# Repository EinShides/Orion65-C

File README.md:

A 65% keyboard PCB that supports standard and arrow key blocker layouts (such as the kbd67) and stepped caps lock. The PCB also features a flex cut for a softer typing experience. Uses USB type C and has a ESD protection diode. PCB is tested and working. A matching case model can be found here via the fusion 360 link: https://a360.co/2X7CGb7 (Though there is a name engraving for myself in the top right that needs to be changed if you don't want it).

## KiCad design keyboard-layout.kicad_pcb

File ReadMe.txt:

The Orion65 pcb is a minimalistic 65% keybaord that is based off and inspired by the voyager60 PCB made by ai03. This PCB uses the same mounting holes as the tada68.

IMPORTANT: Make sure to check and meet the design rules of the chosen pcb manufacturer before ordering or else errors may occur.
		e.g. OSH Park recommends a Pad Mask Clearance of 0.0508mm

This CAD file was created in Kicad version (5.1.5)-3, release build.

Application: KiCad
Version: (5.1.5)-3, release build
Libraries:
    wxWidgets 3.0.4
    libcurl/7.66.0 OpenSSL/1.1.1d (Schannel) zlib/1.2.11 brotli/1.0.7 libidn2/2.2.0 libpsl/0.21.0 (+libidn2/2.1.1) nghttp2/1.39.2
Platform: Windows 8 (build 9200), 64-bit edition, 64 bit, Little endian, wxMSW
Build Info:
    wxWidgets: 3.0.4 (wchar_t,wx containers,compatible with 2.8)
    Boost: 1.71.0
    OpenCASCADE Community Edition: 6.9.1
    Curl: 7.66.0
    Compiler: GCC 9.2.0 with C++ ABI 1013

Build settings:
    USE_WX_GRAPHICS_CONTEXT=OFF
    USE_WX_OVERLAY=OFF
    KICAD_SCRIPTING=ON
    KICAD_SCRIPTING_MODULES=ON
    KICAD_SCRIPTING_PYTHON3=OFF
    KICAD_SCRIPTING_WXPYTHON=ON
    KICAD_SCRIPTING_WXPYTHON_PHOENIX=OFF
    KICAD_SCRIPTING_ACTION_MENU=ON
    BUILD_GITHUB_PLUGIN=ON
    KICAD_USE_OCE=ON
    KICAD_USE_OCC=OFF
    KICAD_SPICE=ON

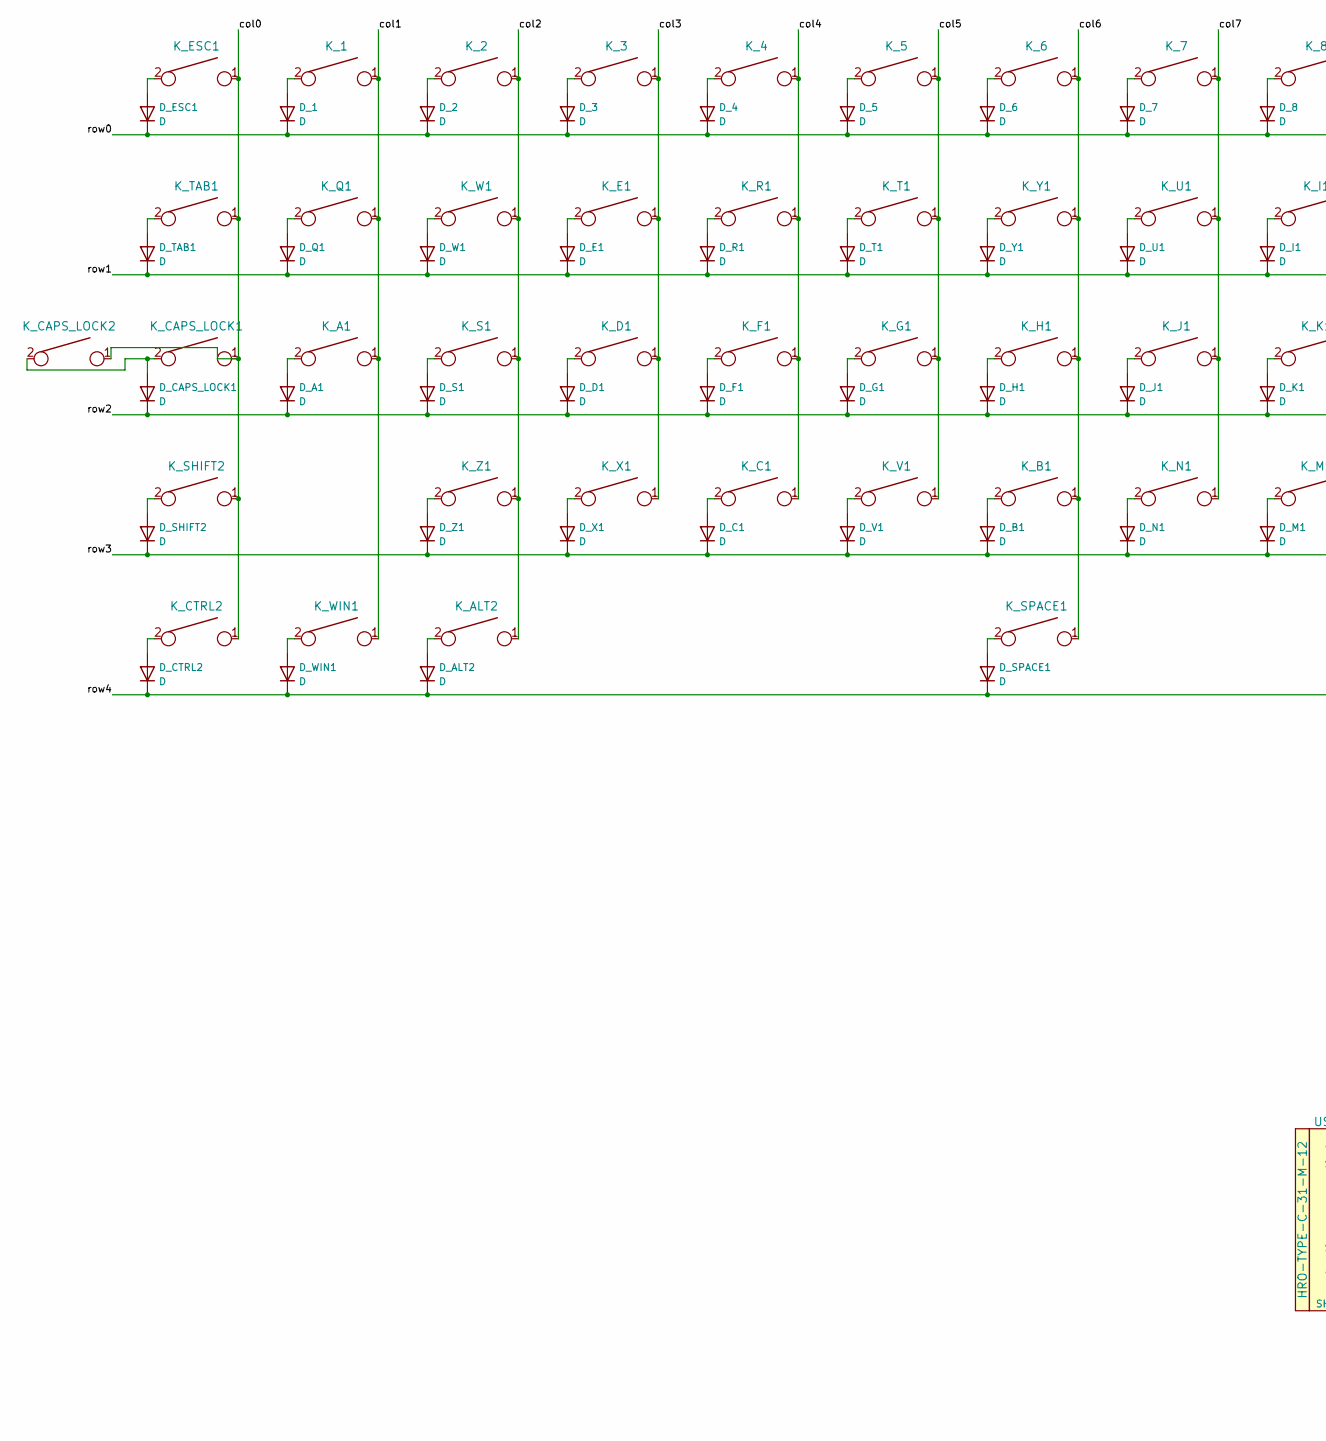
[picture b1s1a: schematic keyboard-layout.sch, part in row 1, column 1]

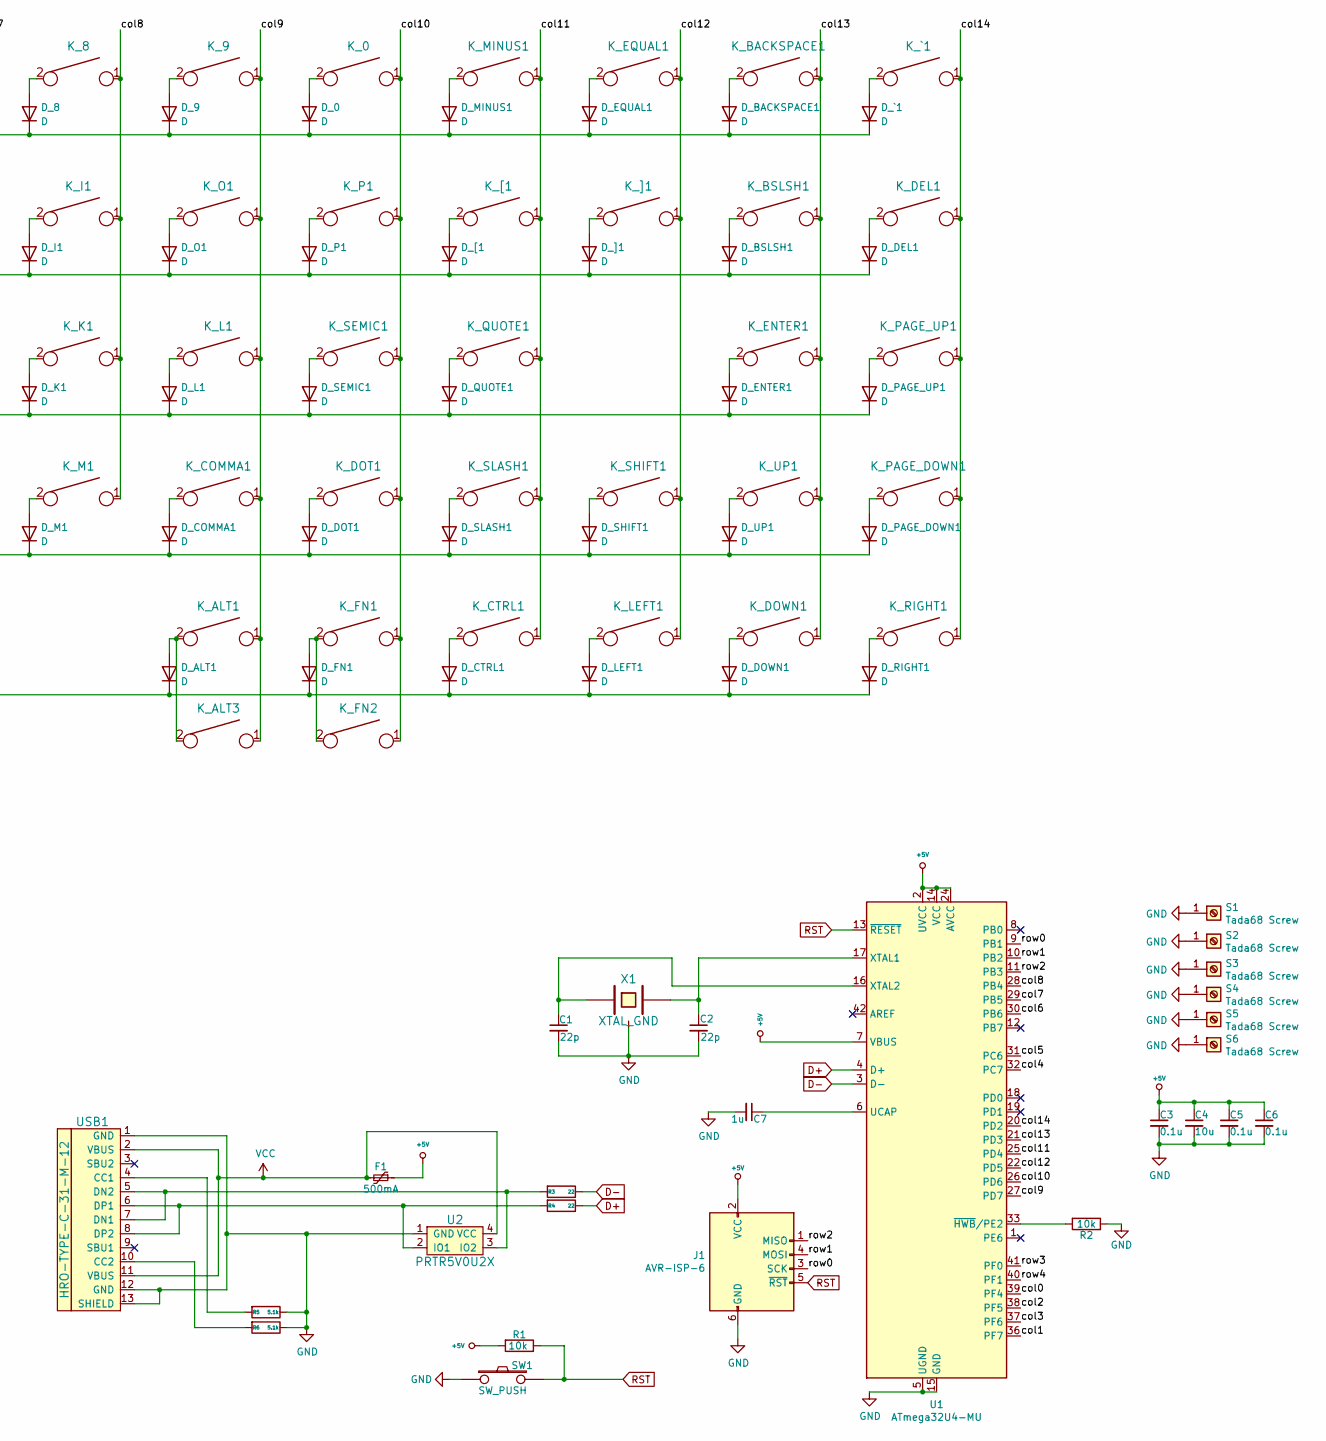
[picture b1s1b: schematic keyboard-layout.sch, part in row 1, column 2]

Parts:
C1, C2: 22p; C_0603_1608Metric_Pad1.05x0.95mm_HandSolder; LCSC C1653
C3, C5, C6: 0.1u; C_0603_1608Metric_Pad1.05x0.95mm_HandSolder; LCSC C24452
C4: 10u; C_0603_1608Metric_Pad1.05x0.95mm_HandSolder; LCSC C96446
C7: 1u; C_0603_1608Metric_Pad1.05x0.95mm_HandSolder; LCSC C15849
D_0, D_1, D_2, D_3, D_4, D_5, D_6, D_7, D_8, D_9: D; D_SOD123_hand; LCSC C64898
D_A1: D; D_SOD123_hand; LCSC C64898
D_ALT1, D_ALT2: D; D_SOD123_hand; LCSC C64898
D_B1: D; D_SOD123_hand; LCSC C64898
D_BACKSPACE1: D; D_SOD123_hand; LCSC C64898
D_BSLSH1: D; D_SOD123_hand; LCSC C64898
D_C1: D; D_SOD123_hand; LCSC C64898
D_CAPS_LOCK1: D; D_SOD123_hand; LCSC C64898
D_COMMA1: D; D_SOD123_hand; LCSC C64898
D_CTRL1, D_CTRL2: D; D_SOD123_hand; LCSC C64898
D_D1: D; D_SOD123_hand; LCSC C64898
D_DEL1: D; D_SOD123_hand; LCSC C64898
D_DOT1: D; D_SOD123_hand; LCSC C64898
D_DOWN1: D; D_SOD123_hand; LCSC C64898
D_E1: D; D_SOD123_hand; LCSC C64898
D_ENTER1: D; D_SOD123_hand; LCSC C64898
D_EQUAL1: D; D_SOD123_hand; LCSC C64898
D_ESC1: D; D_SOD123_hand; LCSC C64898
D_F1: D; D_SOD123_hand; LCSC C64898
D_FN1: D; D_SOD123_hand; LCSC C64898
D_G1: D; D_SOD123_hand; LCSC C64898
D_H1: D; D_SOD123_hand; LCSC C64898
D_I1: D; D_SOD123_hand; LCSC C64898
D_J1: D; D_SOD123_hand; LCSC C64898
D_K1: D; D_SOD123_hand; LCSC C64898
D_L1: D; D_SOD123_hand; LCSC C64898
D_LEFT1: D; D_SOD123_hand; LCSC C64898
D_M1: D; D_SOD123_hand; LCSC C64898
D_MINUS1: D; D_SOD123_hand; LCSC C64898
D_N1: D; D_SOD123_hand; LCSC C64898
D_O1: D; D_SOD123_hand; LCSC C64898
D_P1: D; D_SOD123_hand; LCSC C64898
D_PAGE_DOWN1: D; D_SOD123_hand; LCSC C64898
D_PAGE_UP1: D; D_SOD123_hand; LCSC C64898
D_Q1: D; D_SOD123_hand; LCSC C64898
D_QUOTE1: D; D_SOD123_hand; LCSC C64898
D_R1: D; D_SOD123_hand; LCSC C64898
D_RIGHT1: D; D_SOD123_hand; LCSC C64898
D_S1: D; D_SOD123_hand; LCSC C64898
D_SEMIC1: D; D_SOD123_hand; LCSC C64898
D_SHIFT1, D_SHIFT2: D; D_SOD123_hand; LCSC C64898
D_SLASH1: D; D_SOD123_hand; LCSC C64898
D_SPACE1: D; D_SOD123_hand; LCSC C64898
D_T1: D; D_SOD123_hand; LCSC C64898
D_TAB1: D; D_SOD123_hand; LCSC C64898
D_U1: D; D_SOD123_hand; LCSC C64898
D_UP1: D; D_SOD123_hand; LCSC C64898
D_V1: D; D_SOD123_hand; LCSC C64898
D_W1: D; D_SOD123_hand; LCSC C64898
D_WIN1: D; D_SOD123_hand; LCSC C64898
D_X1: D; D_SOD123_hand; LCSC C64898
D_Y1: D; D_SOD123_hand; LCSC C64898
D_Z1: D; D_SOD123_hand; LCSC C64898
D_[1: D; D_SOD123_hand; LCSC C64898
D_]1: D; D_SOD123_hand; LCSC C64898
D_`1: D; D_SOD123_hand; LCSC C64898
F1: 500mA; Fuse_1206_3216Metric_Pad1.42x1.75mm_HandSolder; LCSC C70076
J1: AVR-ISP-6; isp_standard
K_0, K_1, K_2, K_3, K_4, K_5, K_6, K_7, K_8, K_9: KEYSW; MXOnly-1U-NoLED
K_A1: KEYSW; MXOnly-1U-NoLED
K_ALT1: KEYSW; MXOnly-1U-NoLED
K_ALT2, K_ALT3: KEYSW; MXOnly-1.25U-NoLED
K_B1: KEYSW; MXOnly-1U-NoLED
K_BACKSPACE1: KEYSW; MXOnly-2U-NoLED
K_BSLSH1: KEYSW; MXOnly-1.5U-NoLED
K_C1: KEYSW; MXOnly-1U-NoLED
K_CAPS_LOCK1: KEYSW; MXOnly-1.75U-NoLED
K_CAPS_LOCK2: KEYSW; MXOnly-1.25U-NoLED
K_COMMA1: KEYSW; MXOnly-1U-NoLED
K_CTRL1: KEYSW; MXOnly-1U-NoLED
K_CTRL2: KEYSW; MXOnly-1.25U-NoLED
K_D1: KEYSW; MXOnly-1U-NoLED
K_DEL1: KEYSW; MXOnly-1U-NoLED
K_DOT1: KEYSW; MXOnly-1U-NoLED
K_DOWN1: KEYSW; MXOnly-1U-NoLED
K_E1: KEYSW; MXOnly-1U-NoLED
K_ENTER1: KEYSW; MXOnly-2.25U-NoLED
K_EQUAL1: KEYSW; MXOnly-1U-NoLED
K_ESC1: KEYSW; MXOnly-1U-NoLED
K_F1: KEYSW; MXOnly-1U-NoLED
K_FN1: KEYSW; MXOnly-1U-NoLED
K_FN2: KEYSW; MXOnly-1.25U-NoLED
K_G1: KEYSW; MXOnly-1U-NoLED
K_H1: KEYSW; MXOnly-1U-NoLED
K_I1: KEYSW; MXOnly-1U-NoLED
K_J1: KEYSW; MXOnly-1U-NoLED
K_K1: KEYSW; MXOnly-1U-NoLED
K_L1: KEYSW; MXOnly-1U-NoLED
K_LEFT1: KEYSW; MXOnly-1U-NoLED
K_M1: KEYSW; MXOnly-1U-NoLED
K_MINUS1: KEYSW; MXOnly-1U-NoLED
K_N1: KEYSW; MXOnly-1U-NoLED
K_O1: KEYSW; MXOnly-1U-NoLED
K_P1: KEYSW; MXOnly-1U-NoLED
K_PAGE_DOWN1: KEYSW; MXOnly-1U-NoLED
K_PAGE_UP1: KEYSW; MXOnly-1U-NoLED
K_Q1: KEYSW; MXOnly-1U-NoLED
K_QUOTE1: KEYSW; MXOnly-1U-NoLED
K_R1: KEYSW; MXOnly-1U-NoLED
K_RIGHT1: KEYSW; MXOnly-1U-NoLED
K_S1: KEYSW; MXOnly-1U-NoLED
K_SEMIC1: KEYSW; MXOnly-1U-NoLED
K_SHIFT1: KEYSW; MXOnly-1.75U-NoLED
K_SHIFT2: KEYSW; MXOnly-2.25U-NoLED
K_SLASH1: KEYSW; MXOnly-1U-NoLED
K_SPACE1: KEYSW; MXOnly-6.25U-ReversedStabilizers-NoLED
K_T1: KEYSW; MXOnly-1U-NoLED
K_TAB1: KEYSW; MXOnly-1.5U-NoLED
K_U1: KEYSW; MXOnly-1U-NoLED
K_UP1: KEYSW; MXOnly-1U-NoLED
K_V1: KEYSW; MXOnly-1U-NoLED
K_W1: KEYSW; MXOnly-1U-NoLED
K_WIN1: KEYSW; MXOnly-1.25U-NoLED
K_X1: KEYSW; MXOnly-1U-NoLED
K_Y1: KEYSW; MXOnly-1U-NoLED
K_Z1: KEYSW; MXOnly-1U-NoLED
K_[1: KEYSW; MXOnly-1U-NoLED
K_]1: KEYSW; MXOnly-1U-NoLED
K_`1: KEYSW; MXOnly-1U-NoLED
R1, R2: 10k; R_0805_2012Metric_Pad1.15x1.40mm_HandSolder; LCSC C17414
R3, R4: 22; R_0805_2012Metric_Pad1.15x1.40mm_HandSolder; LCSC C17561
R5, R6: 5.1k; R_0805_2012Metric_Pad1.15x1.40mm_HandSolder; LCSC C27834
S1, S2, S3, S4, S5, S6: Tada68 Screw; 5.5_5x2.5mm
SW1: SW_PUSH; SW_SPST_TL3342
U1: ATmega32U4-MU; QFN-44-1EP_7x7mm_P0.5mm_EP5.2x5.2mm; LCSC C45874
U2: PRTR5V0U2X; SOT143B; LCSC C316030
USB1: HRO-TYPE-C-31-M-12; HRO-TYPE-C-31-M-12-HandSoldering; LCSC C165948
X1: XTAL_GND; crystal_FA238-TSX3225; LCSC C89371

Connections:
+5V: C3.1, C4.1, C5.1, C6.1, F1.1, J1.2 (VCC), R1.2, U1.2 (UVCC), U1.7 (VBUS), U1.14 (VCC), U1.24 (AVCC), U1.34 (VCC), U1.44 (AVCC)
/col0: K_CAPS_LOCK1.1, K_CAPS_LOCK2.1, K_CTRL2.1, K_ESC1.1, K_SHIFT2.1, K_TAB1.1, U1.39 (PF4)
/col1: K_1.1, K_A1.1, K_Q1.1, K_WIN1.1, U1.36 (PF7)
/col2: K_2.1, K_ALT2.1, K_S1.1, K_W1.1, K_Z1.1, U1.38 (PF5)
/col3: K_3.1, K_D1.1, K_E1.1, K_X1.1, U1.37 (PF6)
/col4: K_4.1, K_C1.1, K_F1.1, K_R1.1, U1.32 (PC7)
/col5: K_5.1, K_G1.1, K_T1.1, K_V1.1, U1.31 (PC6)
/col6: K_6.1, K_B1.1, K_H1.1, K_SPACE1.1, K_Y1.1, U1.30 (PB6)
/col7: K_7.1, K_J1.1, K_N1.1, K_U1.1, U1.29 (PB5)
/col8: K_8.1, K_I1.1, K_K1.1, K_M1.1, U1.28 (PB4)
/col9: K_9.1, K_ALT1.1, K_ALT3.1, K_COMMA1.1, K_L1.1, K_O1.1, U1.27 (PD7)
/col10: K_0.1, K_DOT1.1, K_FN1.1, K_FN2.1, K_P1.1, K_SEMIC1.1, U1.26 (PD6)
/col11: K_CTRL1.1, K_MINUS1.1, K_QUOTE1.1, K_SLASH1.1, K_[1.1, U1.25 (PD4)
/col12: K_EQUAL1.1, K_LEFT1.1, K_SHIFT1.1, K_]1.1, U1.22 (PD5)
/col13: K_BACKSPACE1.1, K_BSLSH1.1, K_DOWN1.1, K_ENTER1.1, K_UP1.1, U1.21 (PD3)
/col14: K_DEL1.1, K_PAGE_DOWN1.1, K_PAGE_UP1.1, K_RIGHT1.1, K_`1.1, U1.20 (PD2)
/row0: D_0.1 (K), D_1.1 (K), D_2.1 (K), D_3.1 (K), D_4.1 (K), D_5.1 (K), D_6.1 (K), D_7.1 (K), D_8.1 (K), D_9.1 (K), D_BACKSPACE1.1 (K), D_EQUAL1.1 (K), D_ESC1.1 (K), D_MINUS1.1 (K), D_`1.1 (K), J1.3 (SCK), U1.9 (PB1)
/row1: D_BSLSH1.1 (K), D_DEL1.1 (K), D_E1.1 (K), D_I1.1 (K), D_O1.1 (K), D_P1.1 (K), D_Q1.1 (K), D_R1.1 (K), D_T1.1 (K), D_TAB1.1 (K), D_U1.1 (K), D_W1.1 (K), D_Y1.1 (K), D_[1.1 (K), D_]1.1 (K), J1.4 (MOSI), U1.10 (PB2)
/row2: D_A1.1 (K), D_CAPS_LOCK1.1 (K), D_D1.1 (K), D_ENTER1.1 (K), D_F1.1 (K), D_G1.1 (K), D_H1.1 (K), D_J1.1 (K), D_K1.1 (K), D_L1.1 (K), D_PAGE_UP1.1 (K), D_QUOTE1.1 (K), D_S1.1 (K), D_SEMIC1.1 (K), J1.1 (MISO), U1.11 (PB3)
/row3: D_B1.1 (K), D_C1.1 (K), D_COMMA1.1 (K), D_DOT1.1 (K), D_M1.1 (K), D_N1.1 (K), D_PAGE_DOWN1.1 (K), D_SHIFT1.1 (K), D_SHIFT2.1 (K), D_SLASH1.1 (K), D_UP1.1 (K), D_V1.1 (K), D_X1.1 (K), D_Z1.1 (K), U1.41 (PF0)
/row4: D_ALT1.1 (K), D_ALT2.1 (K), D_CTRL1.1 (K), D_CTRL2.1 (K), D_DOWN1.1 (K), D_FN1.1 (K), D_LEFT1.1 (K), D_RIGHT1.1 (K), D_SPACE1.1 (K), D_WIN1.1 (K), U1.40 (PF1)
D+: R4.1, U1.4 (D+)
D-: R3.1, U1.3 (D-)
GND: C1.2, C2.2, C3.2, C4.2, C5.2, C6.2, C7.2, J1.6 (GND), R2.1, R5.1, R6.1, S1.1, S2.1, S3.1, S4.1, S5.1, S6.1, SW1.1, U1.5 (UGND), U1.15 (GND), U1.23 (GND), U1.35 (GND), U1.43 (GND), U1.45 (GND), U2.1 (GND), USB1.1 (GND), USB1.12 (GND), USB1.13 (SHIELD), X1.3
unnamed: C1.1, U1.16 (XTAL2), X1.1
unnamed: C2.1, U1.17 (XTAL1), X1.2
unnamed: C7.1, U1.6 (UCAP)
unnamed: D_0.2 (A), K_0.2
unnamed: D_1.2 (A), K_1.2
unnamed: D_2.2 (A), K_2.2
unnamed: D_3.2 (A), K_3.2
unnamed: D_4.2 (A), K_4.2
unnamed: D_5.2 (A), K_5.2
unnamed: D_6.2 (A), K_6.2
unnamed: D_7.2 (A), K_7.2
unnamed: D_8.2 (A), K_8.2
unnamed: D_9.2 (A), K_9.2
unnamed: D_A1.2 (A), K_A1.2
unnamed: D_ALT1.2 (A), K_ALT1.2, K_ALT3.2
unnamed: D_ALT2.2 (A), K_ALT2.2
unnamed: D_B1.2 (A), K_B1.2
unnamed: D_BACKSPACE1.2 (A), K_BACKSPACE1.2
unnamed: D_BSLSH1.2 (A), K_BSLSH1.2
unnamed: D_C1.2 (A), K_C1.2
unnamed: D_CAPS_LOCK1.2 (A), K_CAPS_LOCK1.2, K_CAPS_LOCK2.2
unnamed: D_COMMA1.2 (A), K_COMMA1.2
unnamed: D_CTRL1.2 (A), K_CTRL1.2
unnamed: D_CTRL2.2 (A), K_CTRL2.2
unnamed: D_D1.2 (A), K_D1.2
unnamed: D_DEL1.2 (A), K_DEL1.2
unnamed: D_DOT1.2 (A), K_DOT1.2
unnamed: D_DOWN1.2 (A), K_DOWN1.2
unnamed: D_E1.2 (A), K_E1.2
unnamed: D_ENTER1.2 (A), K_ENTER1.2
unnamed: D_EQUAL1.2 (A), K_EQUAL1.2
unnamed: D_ESC1.2 (A), K_ESC1.2
unnamed: D_F1.2 (A), K_F1.2
unnamed: D_FN1.2 (A), K_FN1.2, K_FN2.2
unnamed: D_G1.2 (A), K_G1.2
unnamed: D_H1.2 (A), K_H1.2
unnamed: D_I1.2 (A), K_I1.2
unnamed: D_J1.2 (A), K_J1.2
unnamed: D_K1.2 (A), K_K1.2
unnamed: D_L1.2 (A), K_L1.2
unnamed: D_LEFT1.2 (A), K_LEFT1.2
unnamed: D_M1.2 (A), K_M1.2
unnamed: D_MINUS1.2 (A), K_MINUS1.2
unnamed: D_N1.2 (A), K_N1.2
unnamed: D_O1.2 (A), K_O1.2
unnamed: D_P1.2 (A), K_P1.2
unnamed: D_PAGE_DOWN1.2 (A), K_PAGE_DOWN1.2
unnamed: D_PAGE_UP1.2 (A), K_PAGE_UP1.2
unnamed: D_Q1.2 (A), K_Q1.2
unnamed: D_QUOTE1.2 (A), K_QUOTE1.2
unnamed: D_R1.2 (A), K_R1.2
unnamed: D_RIGHT1.2 (A), K_RIGHT1.2
unnamed: D_S1.2 (A), K_S1.2
unnamed: D_SEMIC1.2 (A), K_SEMIC1.2
unnamed: D_SHIFT1.2 (A), K_SHIFT1.2
unnamed: D_SHIFT2.2 (A), K_SHIFT2.2
unnamed: D_SLASH1.2 (A), K_SLASH1.2
unnamed: D_SPACE1.2 (A), K_SPACE1.2
unnamed: D_T1.2 (A), K_T1.2
unnamed: D_TAB1.2 (A), K_TAB1.2
unnamed: D_U1.2 (A), K_U1.2
unnamed: D_UP1.2 (A), K_UP1.2
unnamed: D_V1.2 (A), K_V1.2
unnamed: D_W1.2 (A), K_W1.2
unnamed: D_WIN1.2 (A), K_WIN1.2
unnamed: D_X1.2 (A), K_X1.2
unnamed: D_Y1.2 (A), K_Y1.2
unnamed: D_Z1.2 (A), K_Z1.2
unnamed: D_[1.2 (A), K_[1.2
unnamed: D_]1.2 (A), K_]1.2
unnamed: D_`1.2 (A), K_`1.2
unnamed: R2.2, U1.33 (~HWB~/PE2)
unnamed: R3.2, U2.3 (IO2), USB1.5 (DN2), USB1.7 (DN1)
unnamed: R4.2, U2.2 (IO1), USB1.6 (DP1), USB1.8 (DP2)
unnamed: R5.2, USB1.4 (CC1)
unnamed: R6.2, USB1.10 (CC2)
RST: J1.5 (~RST), R1.1, SW1.2, U1.13 (~RESET)
VCC: F1.2, U2.4 (VCC), USB1.2 (VBUS), USB1.11 (VBUS)

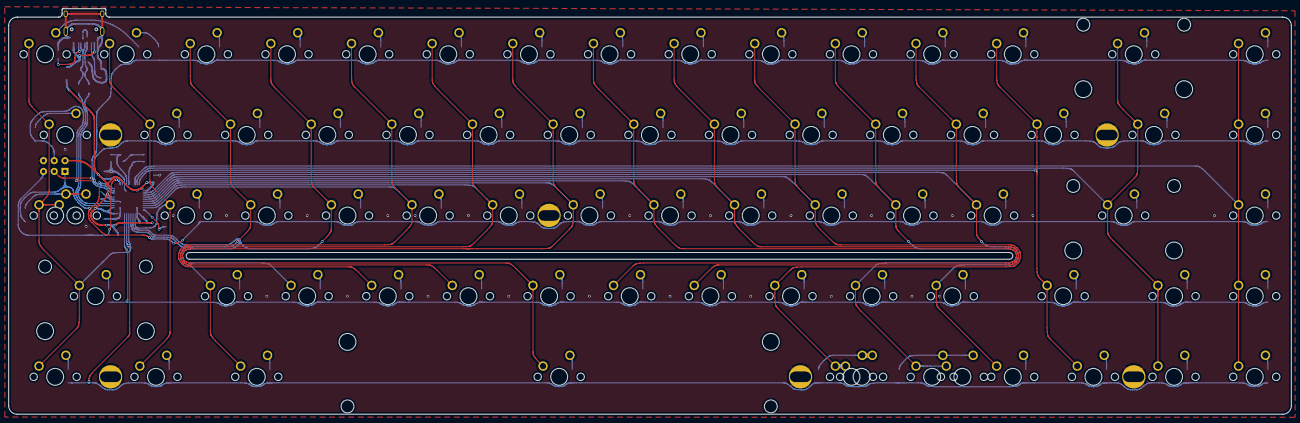
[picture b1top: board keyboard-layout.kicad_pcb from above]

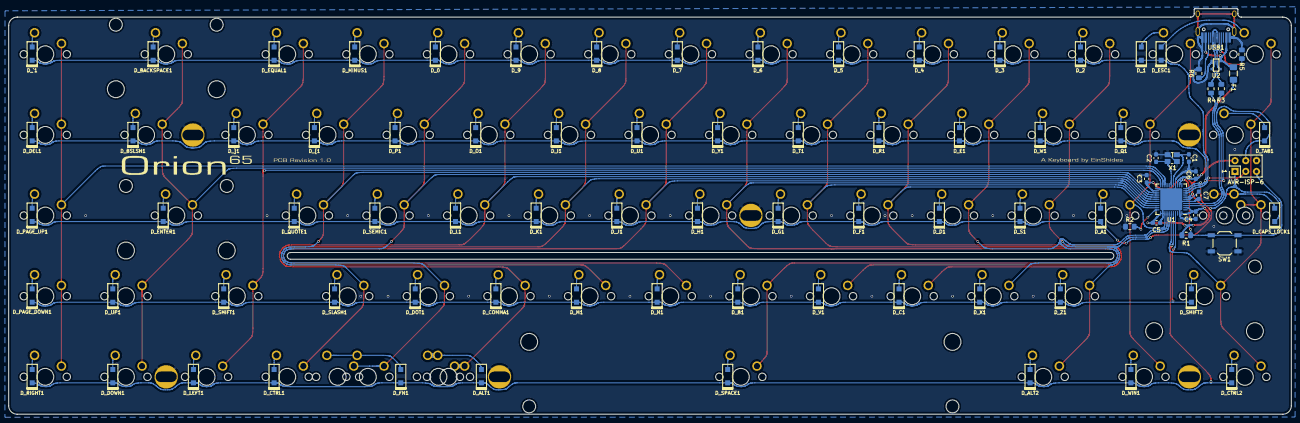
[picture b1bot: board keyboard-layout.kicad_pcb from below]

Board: 2 copper layers, 303.0 x 95.8 mm, 165 parts (88 on the bottom side), 102 nets.
